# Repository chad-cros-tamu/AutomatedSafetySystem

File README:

The hardware folder folder is for the hardware designs of the main controller board, the light curtain and the proximity sensor
The firmware folder is for the code that runs the MCU.

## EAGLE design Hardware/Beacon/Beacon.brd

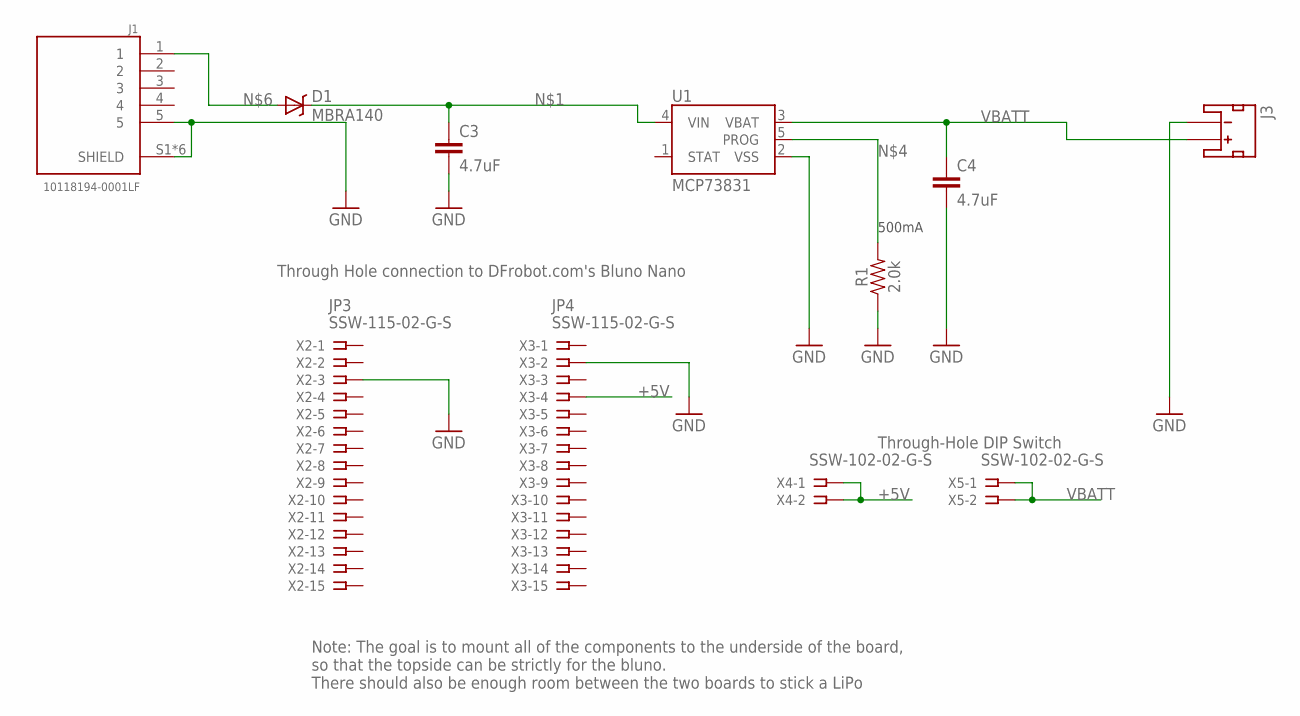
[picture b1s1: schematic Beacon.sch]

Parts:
C3, C4: 4.7uF; 0603
D1: MBRA140; SMA-DIODE
J1: 10118194-0001LF; AMPHENOL_10118194-0001LF
J3: JST_2MM_MALE; JST-2-SMD
R1: 2.0k; 0603
U1: MCP73831; SOT23-5
X2, X3: SSW-115-02-G-S
X4, X5: SSW-102-02-G-S

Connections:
+5V: X3.4, X4.1, X4.2
GND: C3.2, C4.2, J1.5, J1.S1 (SHIELD), J1.S2 (SHIELD), J1.S3 (SHIELD), J1.S4 (SHIELD), J1.S5 (SHIELD), J1.S6 (SHIELD), J3.1 (-), R1.1, U1.2 (VSS), X2.3, X3.2
unnamed: C3.1, D1.C, U1.4 (VIN)
unnamed: R1.2, U1.5 (PROG)
unnamed: D1.A, J1.1
VBATT: C4.1, J3.2 (+), U1.3 (VBAT), X5.1, X5.2

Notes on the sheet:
500mA
JP3
JP4
Through-Hole DIP Switch
Through Hole connection to DFrobot.com's Bluno Nano
Note: The goal is to mount all of the components to the underside of the board, so that the topside can be strictly for the bluno. There should also be enough room between the two boards to stick a LiPo

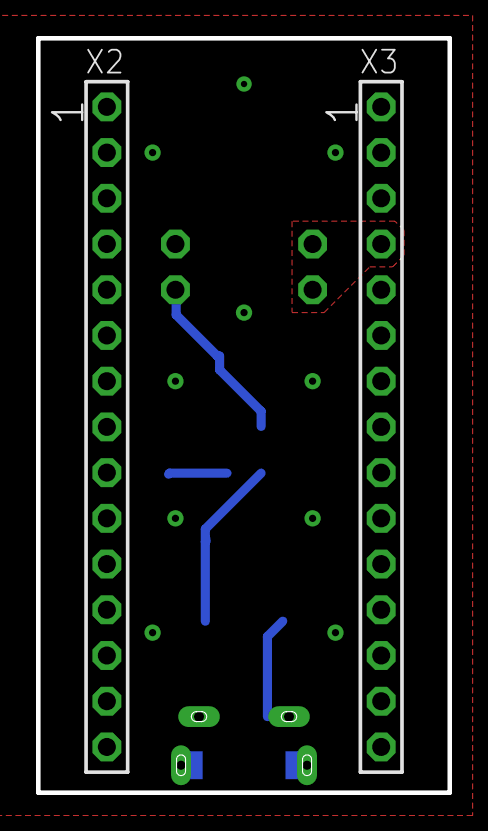
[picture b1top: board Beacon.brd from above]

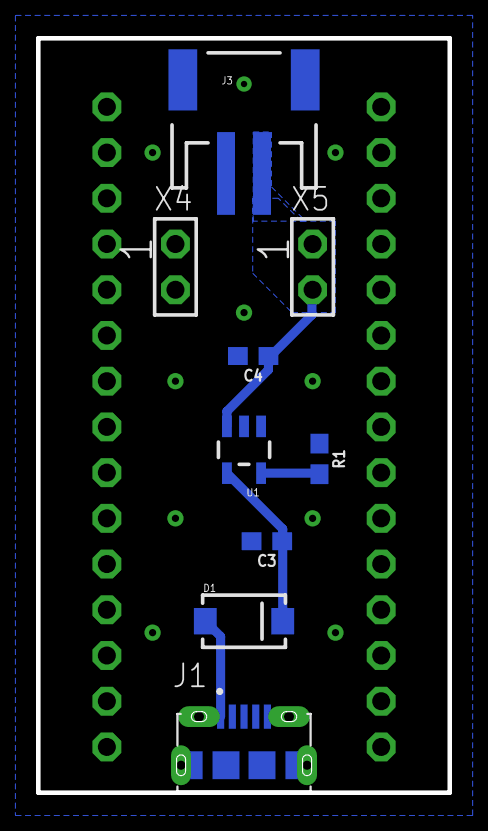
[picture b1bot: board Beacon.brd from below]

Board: 2 copper layers, 22.9 x 41.9 mm, 11 parts (9 on the bottom side), 6 nets.

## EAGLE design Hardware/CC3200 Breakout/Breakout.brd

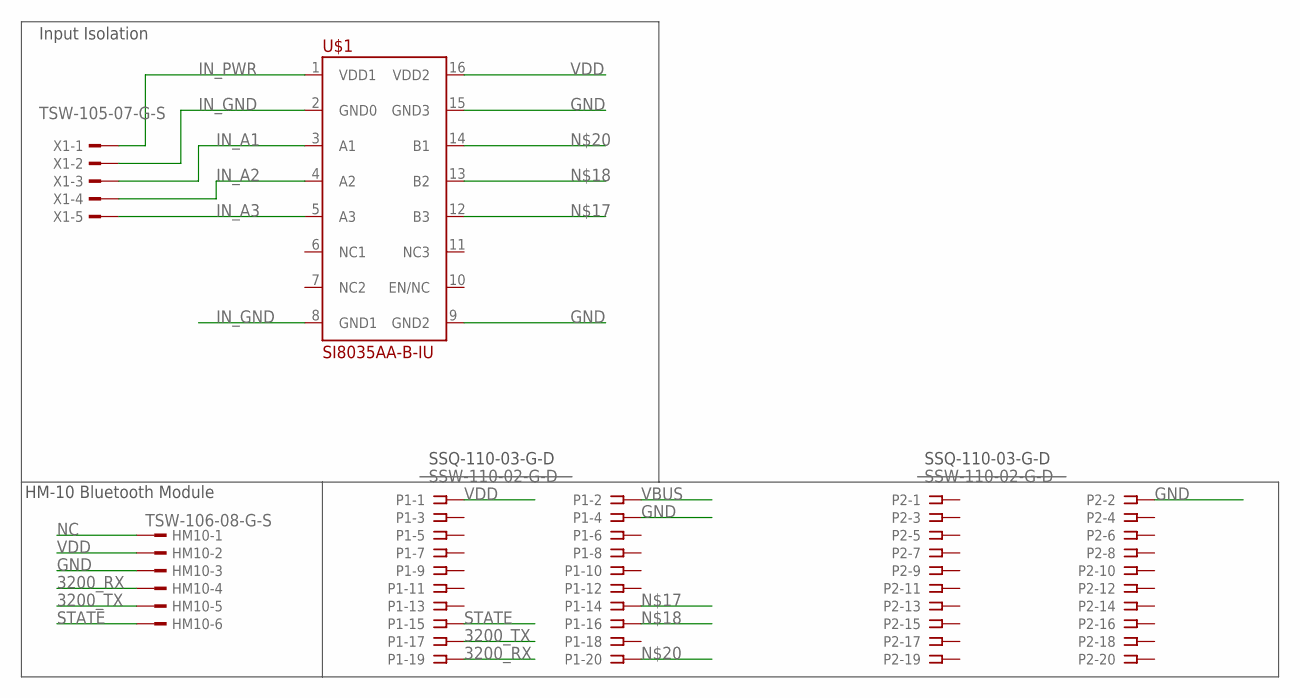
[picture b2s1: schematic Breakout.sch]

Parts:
HM10: TSW-106-08-G-S; TSW-106-XX-G-S
P1, P2: SSW-110-02-G-D
U$1: SI8035AA-B-IU; SOP63P602X175-16N
X1: TSW-105-07-G-S; TSW-105-XX-G-S

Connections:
3200_RX: HM10.4, P1.19
3200_TX: HM10.5, P1.17
GND: HM10.3, P1.4, P2.2, U$1.9 (GND2), U$1.15 (GND3)
IN_A1: U$1.3 (A1), X1.3
IN_A2: U$1.4 (A2), X1.4
IN_A3: U$1.5 (A3), X1.5
IN_GND: U$1.2 (GND0), U$1.8 (GND1), X1.2
IN_PWR: U$1.1 (VDD1), X1.1
unnamed: P1.14, U$1.12 (B3)
unnamed: P1.16, U$1.13 (B2)
unnamed: P1.20, U$1.14 (B1)
NC: HM10.1
STATE: HM10.6, P1.15
VBUS: P1.2
VDD: HM10.2, P1.1, U$1.16 (VDD2)

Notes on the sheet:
HM-10 Bluetooth Module
SSQ-110-03-G-D
Input Isolation

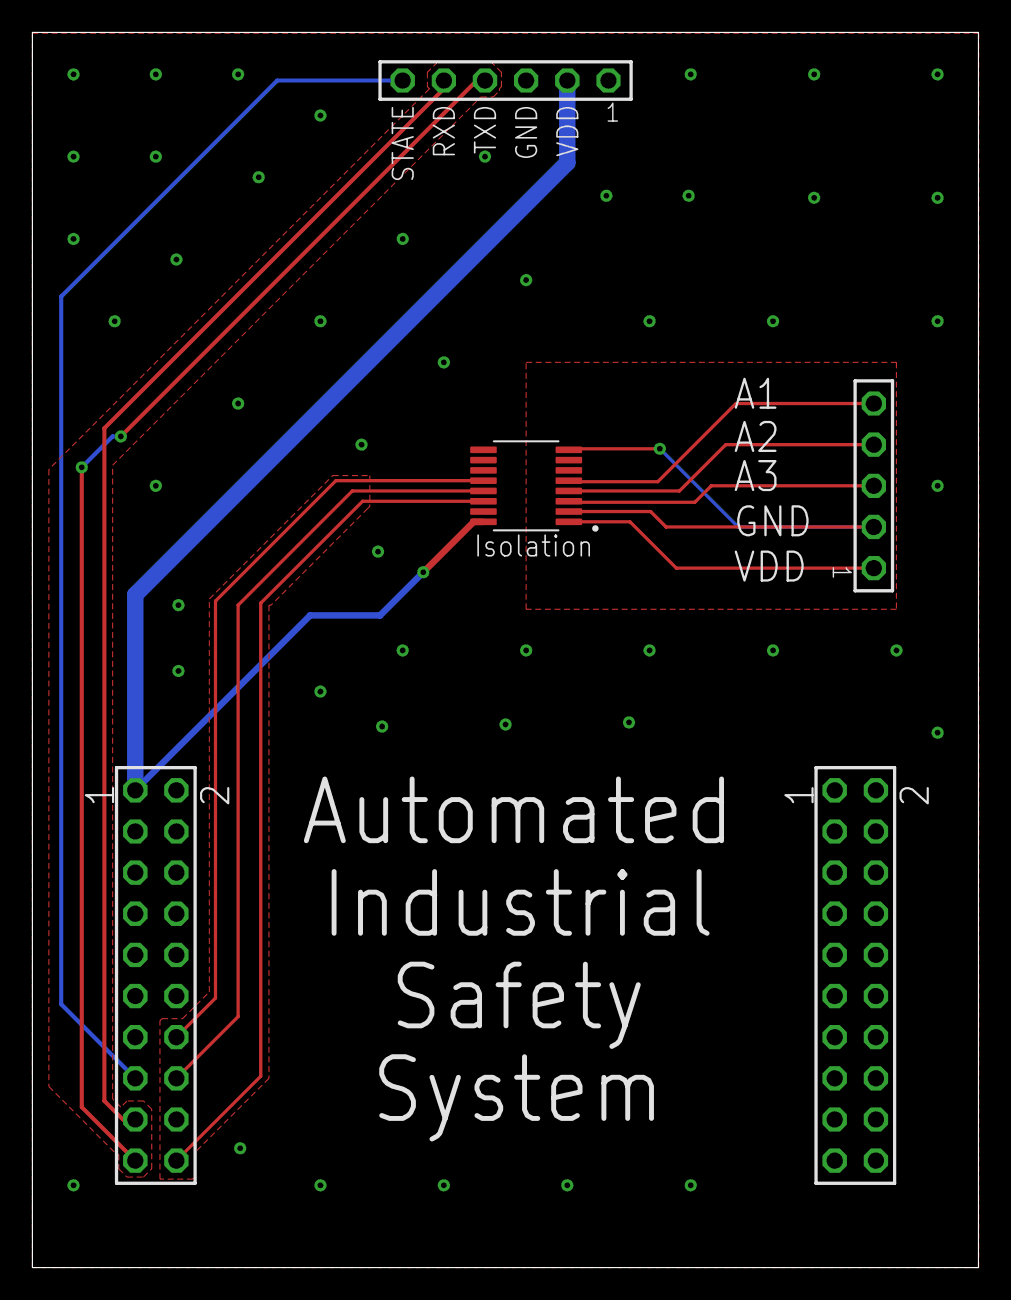
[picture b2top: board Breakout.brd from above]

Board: 2 copper layers, 58.4 x 76.3 mm, 5 parts (0 on the bottom side), 13 nets.

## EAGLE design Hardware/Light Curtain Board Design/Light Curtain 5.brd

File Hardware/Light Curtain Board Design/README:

Design and validation of light curtain sensor

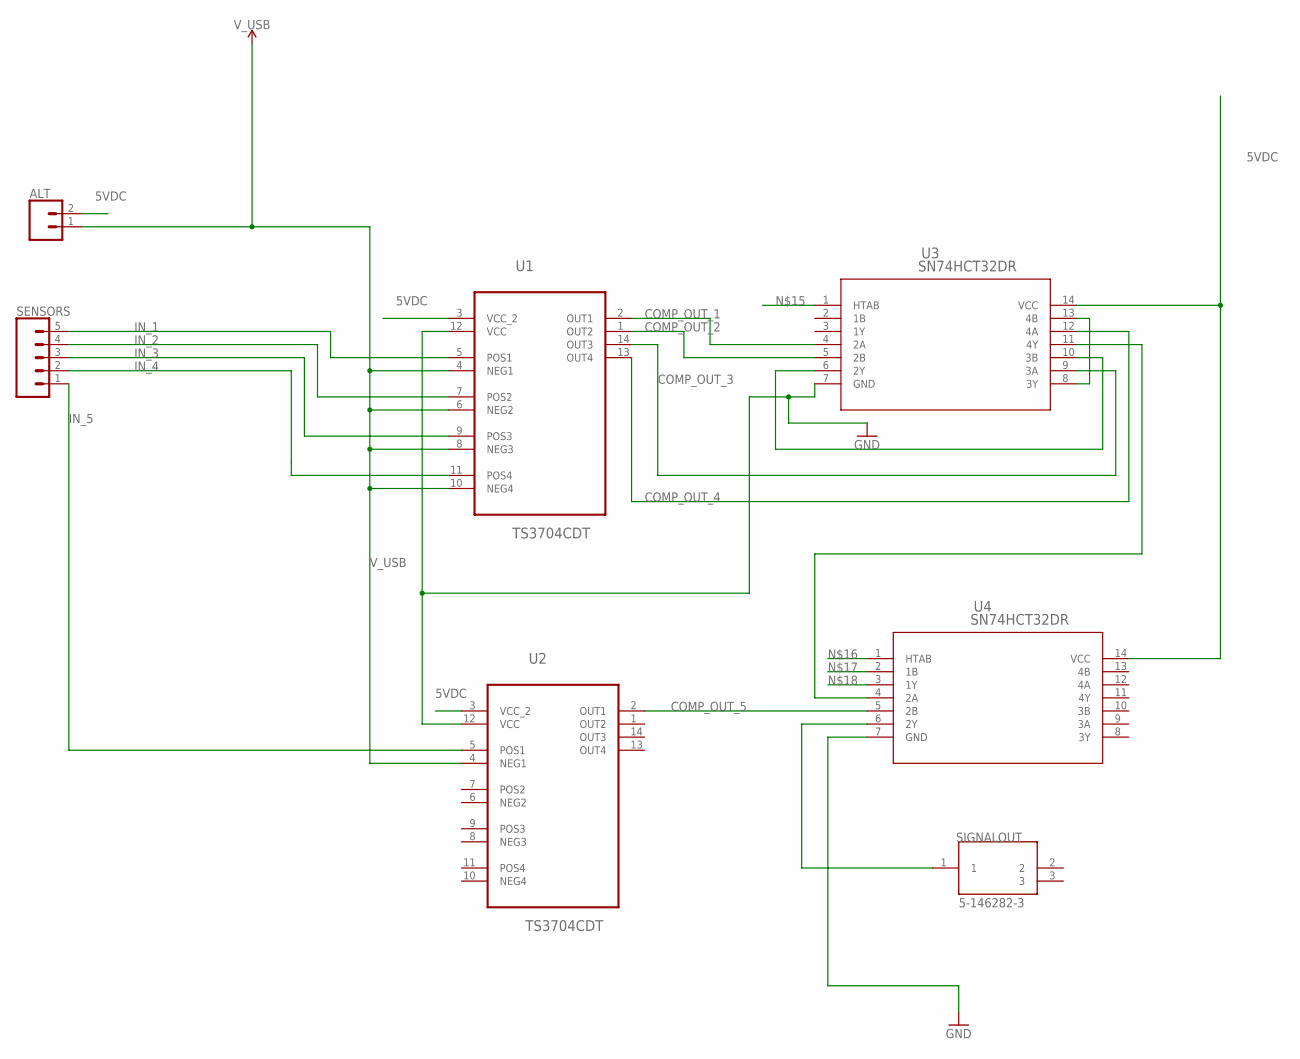
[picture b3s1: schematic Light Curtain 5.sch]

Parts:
ALT: CONN_02; 1X02
SENSORS: CONN_05; 1X05
SIGNALOUT: 5-146282-3; TE_5-146282-3
U1, U2: TS3704CDT; SOIC127P600X175-14N
U3, U4: SN74HCT32DR; D14

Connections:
5VDC: ALT.2, U1.3 (VCC_2), U2.3 (VCC_2), U3.14 (VCC), U4.14 (VCC)
COMP_OUT_1: U1.2 (OUT1), U3.4 (2A)
COMP_OUT_2: U1.1 (OUT2), U3.5 (2B)
COMP_OUT_3: U1.14 (OUT3), U3.9 (3A)
COMP_OUT_4: U1.13 (OUT4), U3.12 (4A)
COMP_OUT_5: U2.2 (OUT1), U4.5 (2B)
GND: U1.12 (VCC), U2.12 (VCC), U3.7 (GND), U4.7 (GND)
IN_1: SENSORS.5, U1.5 (POS1)
IN_2: SENSORS.4, U1.7 (POS2)
IN_3: SENSORS.3, U1.9 (POS3)
IN_4: SENSORS.2, U1.11 (POS4)
IN_5: SENSORS.1, U2.5 (POS1)
unnamed: U3.6 (2Y), U3.10 (3B)
unnamed: U3.8 (3Y), U3.13 (4B)
unnamed: U3.11 (4Y), U4.4 (2A)
unnamed: SIGNALOUT.1, U4.6 (2Y)
V_USB: ALT.1, U1.4 (NEG1), U1.6 (NEG2), U1.8 (NEG3), U1.10 (NEG4), U2.4 (NEG1)

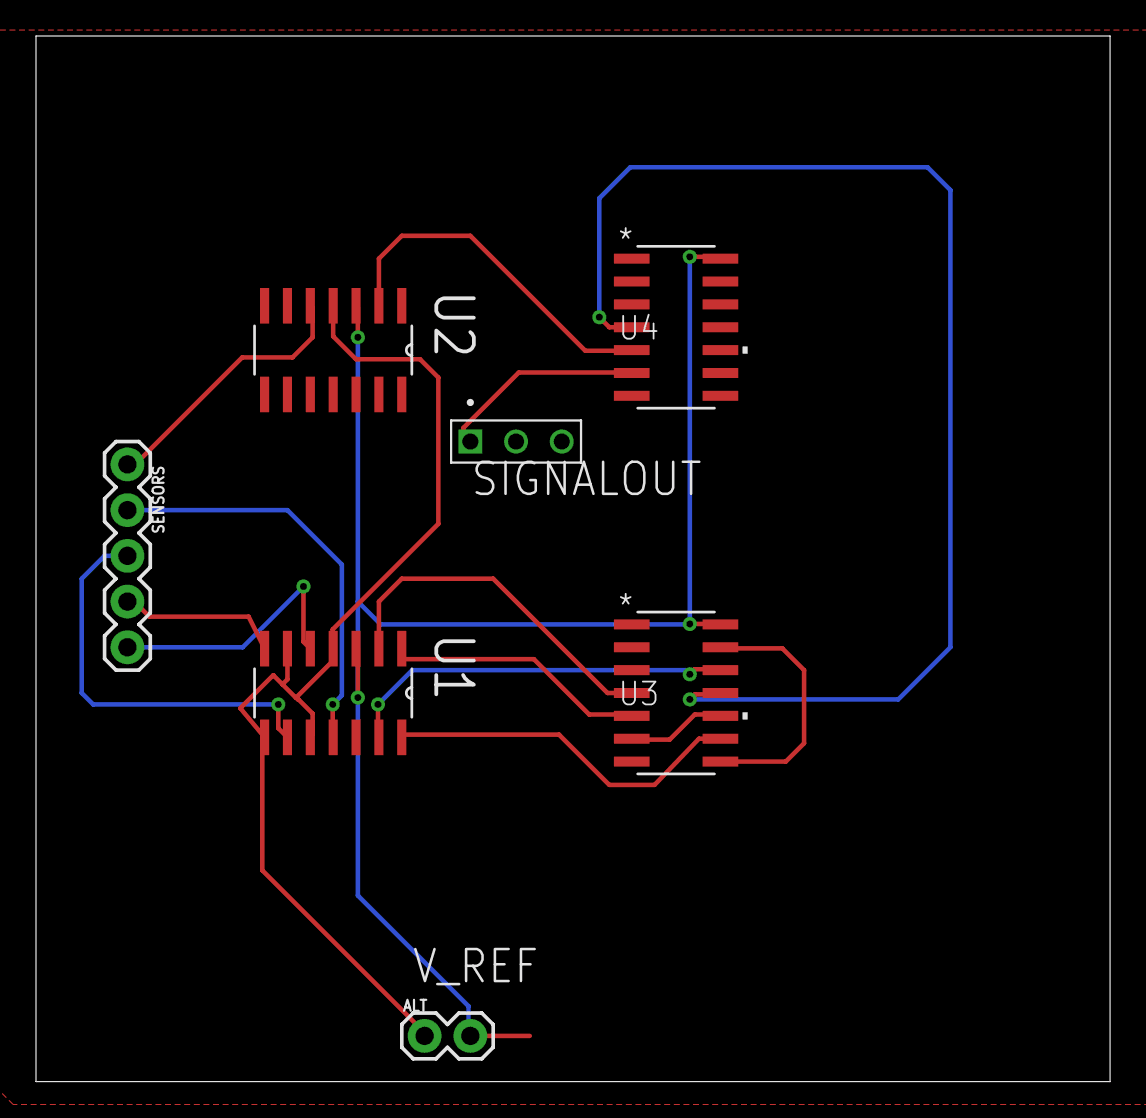
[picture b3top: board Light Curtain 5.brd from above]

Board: 2 copper layers, 59.7 x 58.1 mm, 7 parts (0 on the bottom side), 17 nets.

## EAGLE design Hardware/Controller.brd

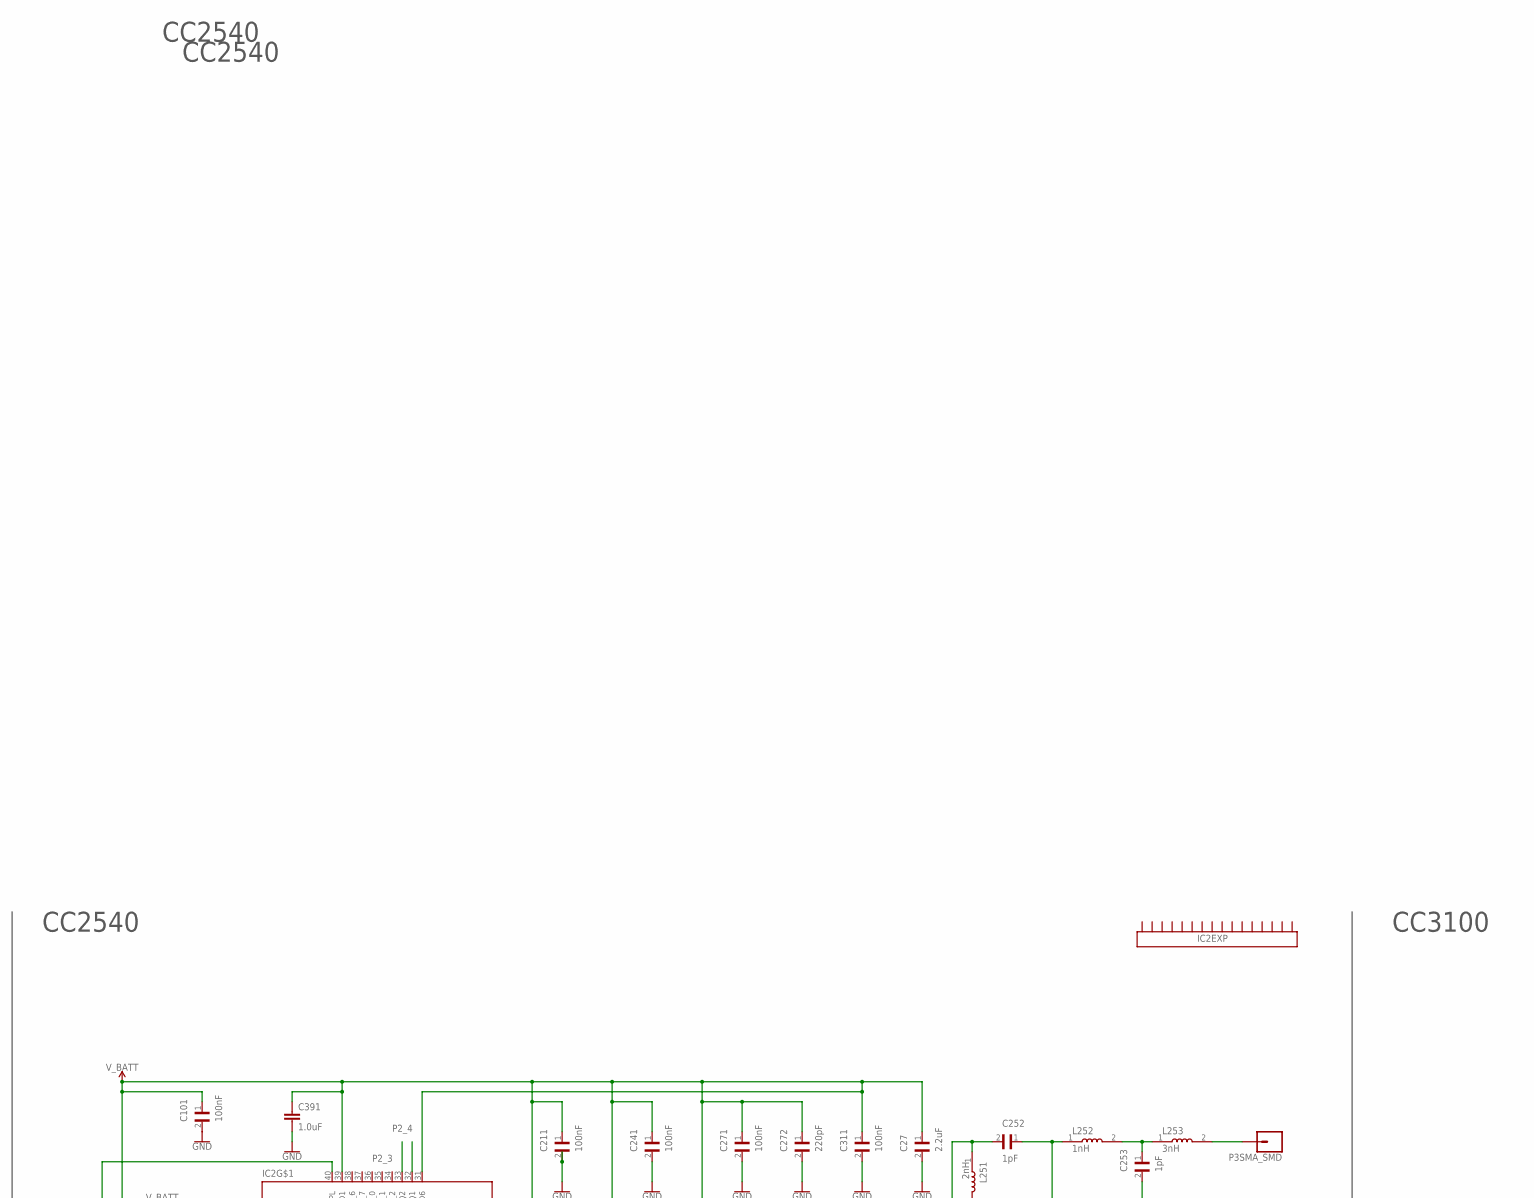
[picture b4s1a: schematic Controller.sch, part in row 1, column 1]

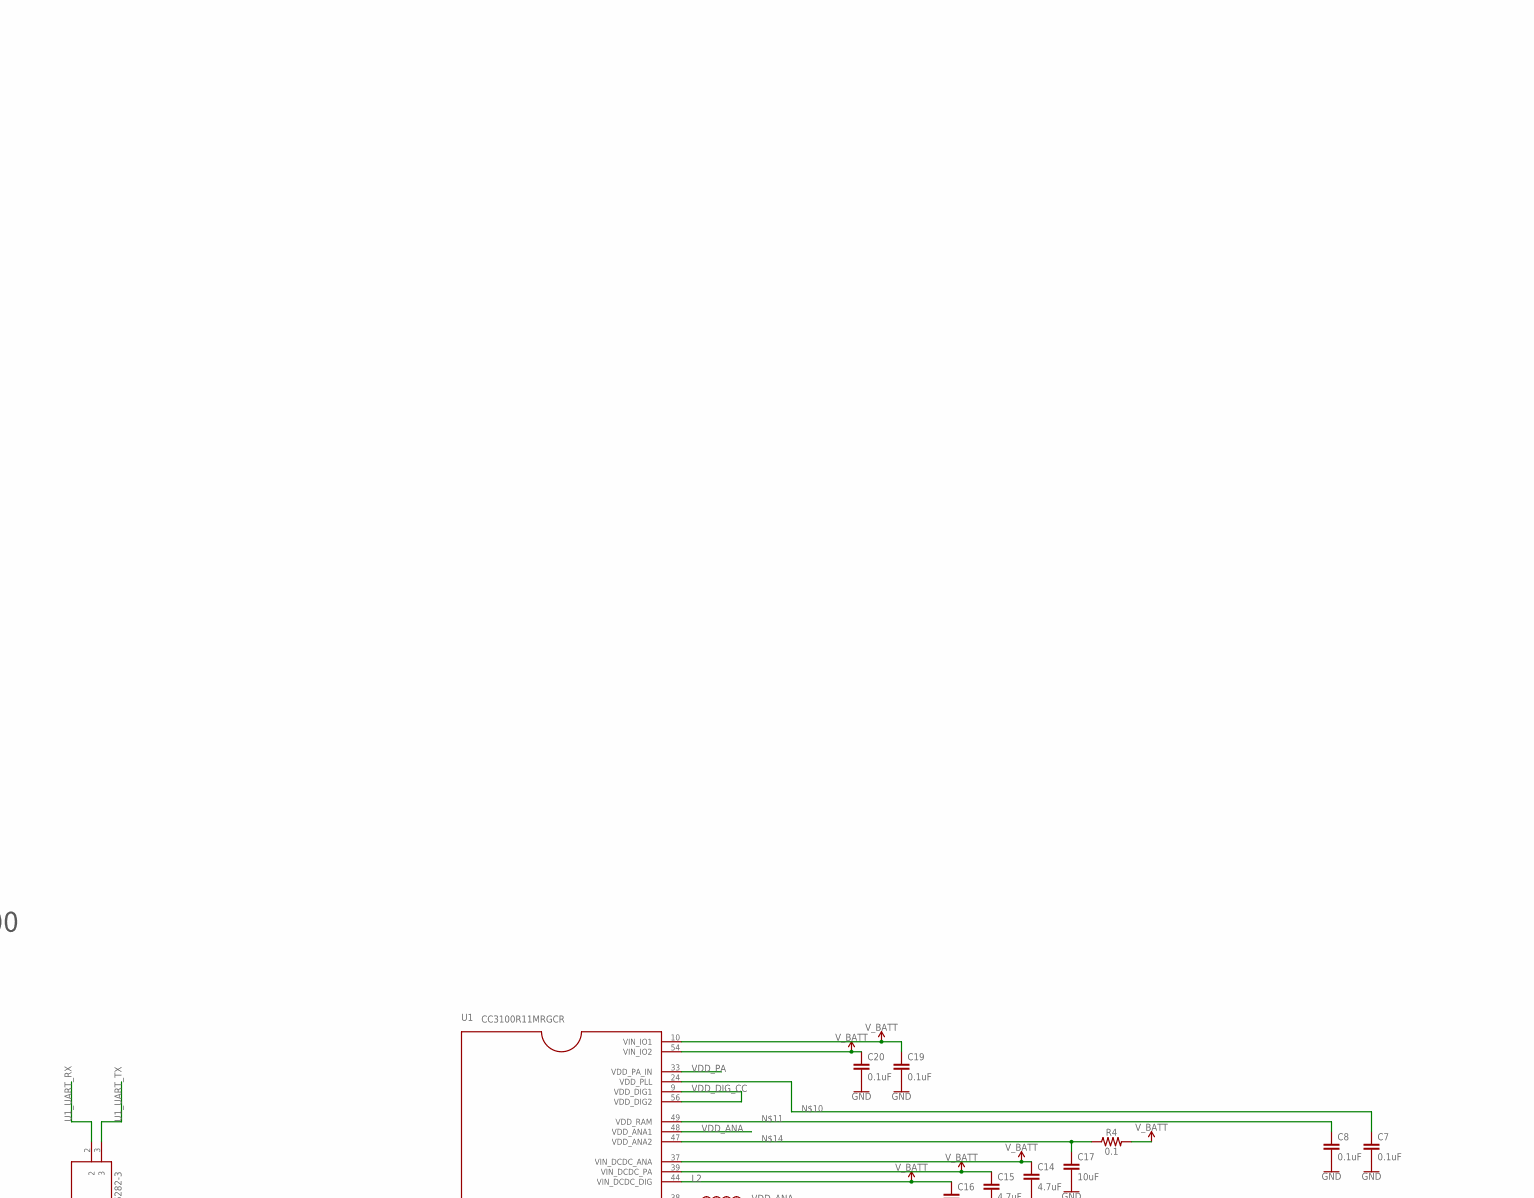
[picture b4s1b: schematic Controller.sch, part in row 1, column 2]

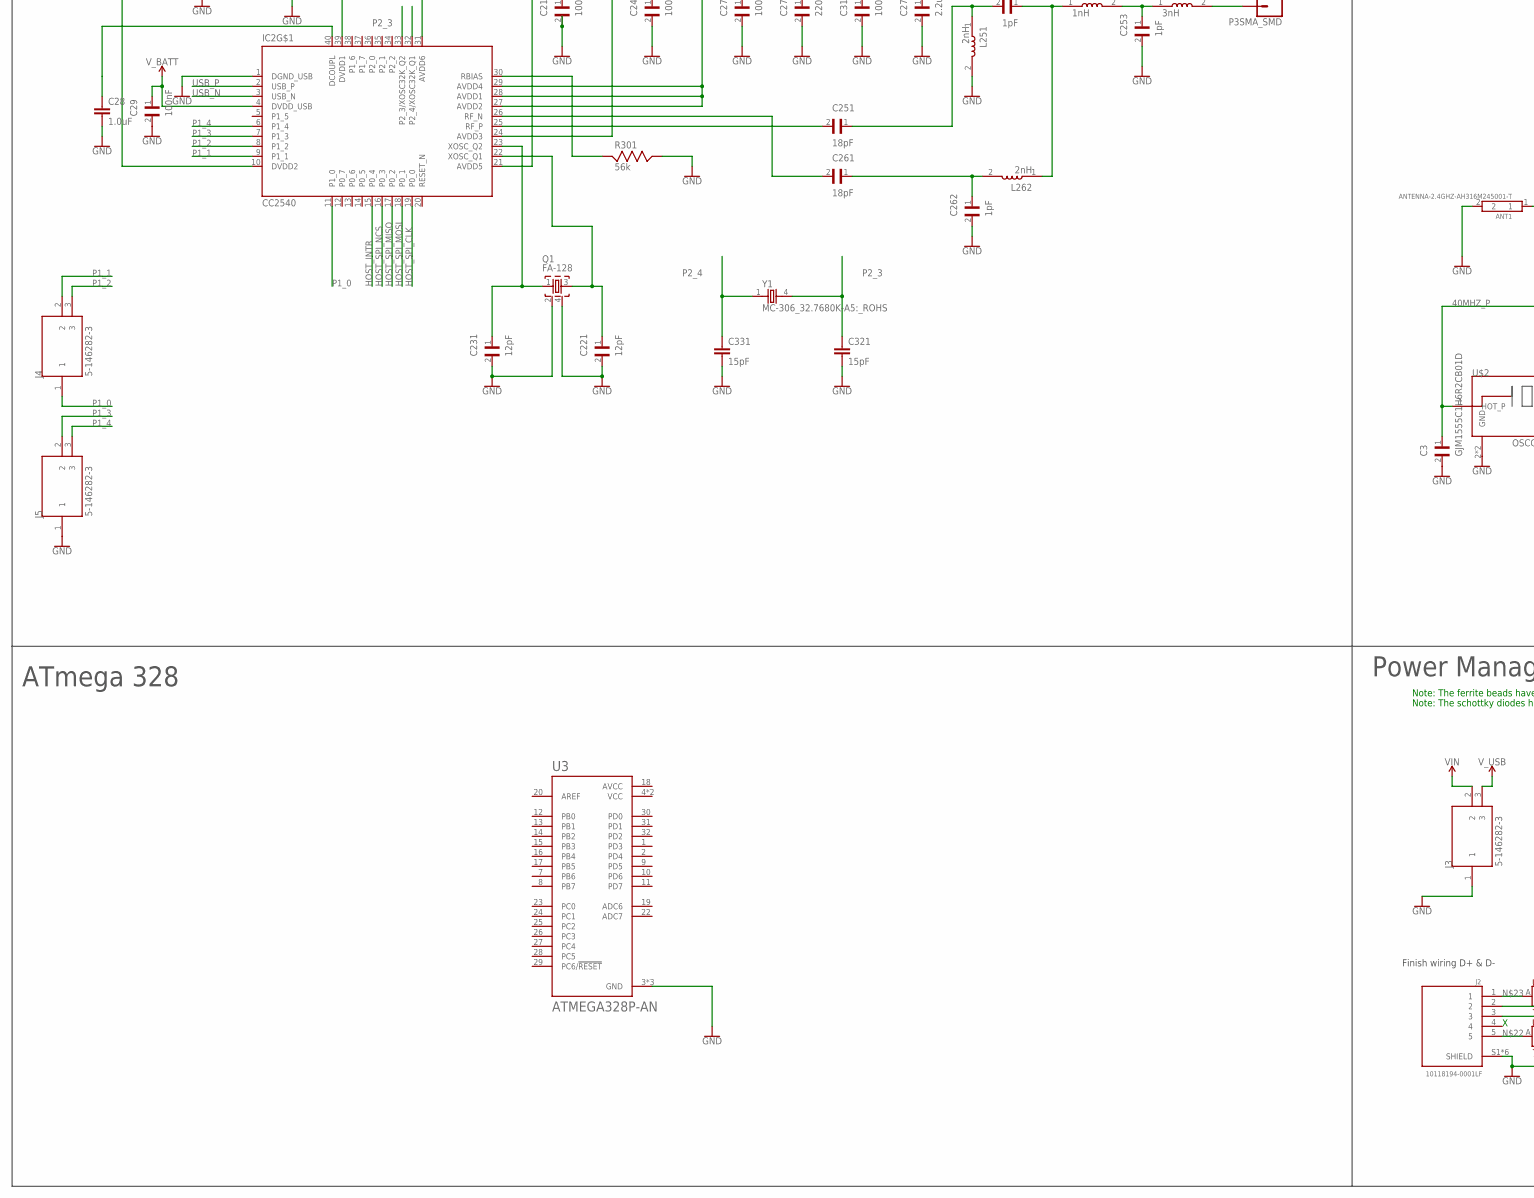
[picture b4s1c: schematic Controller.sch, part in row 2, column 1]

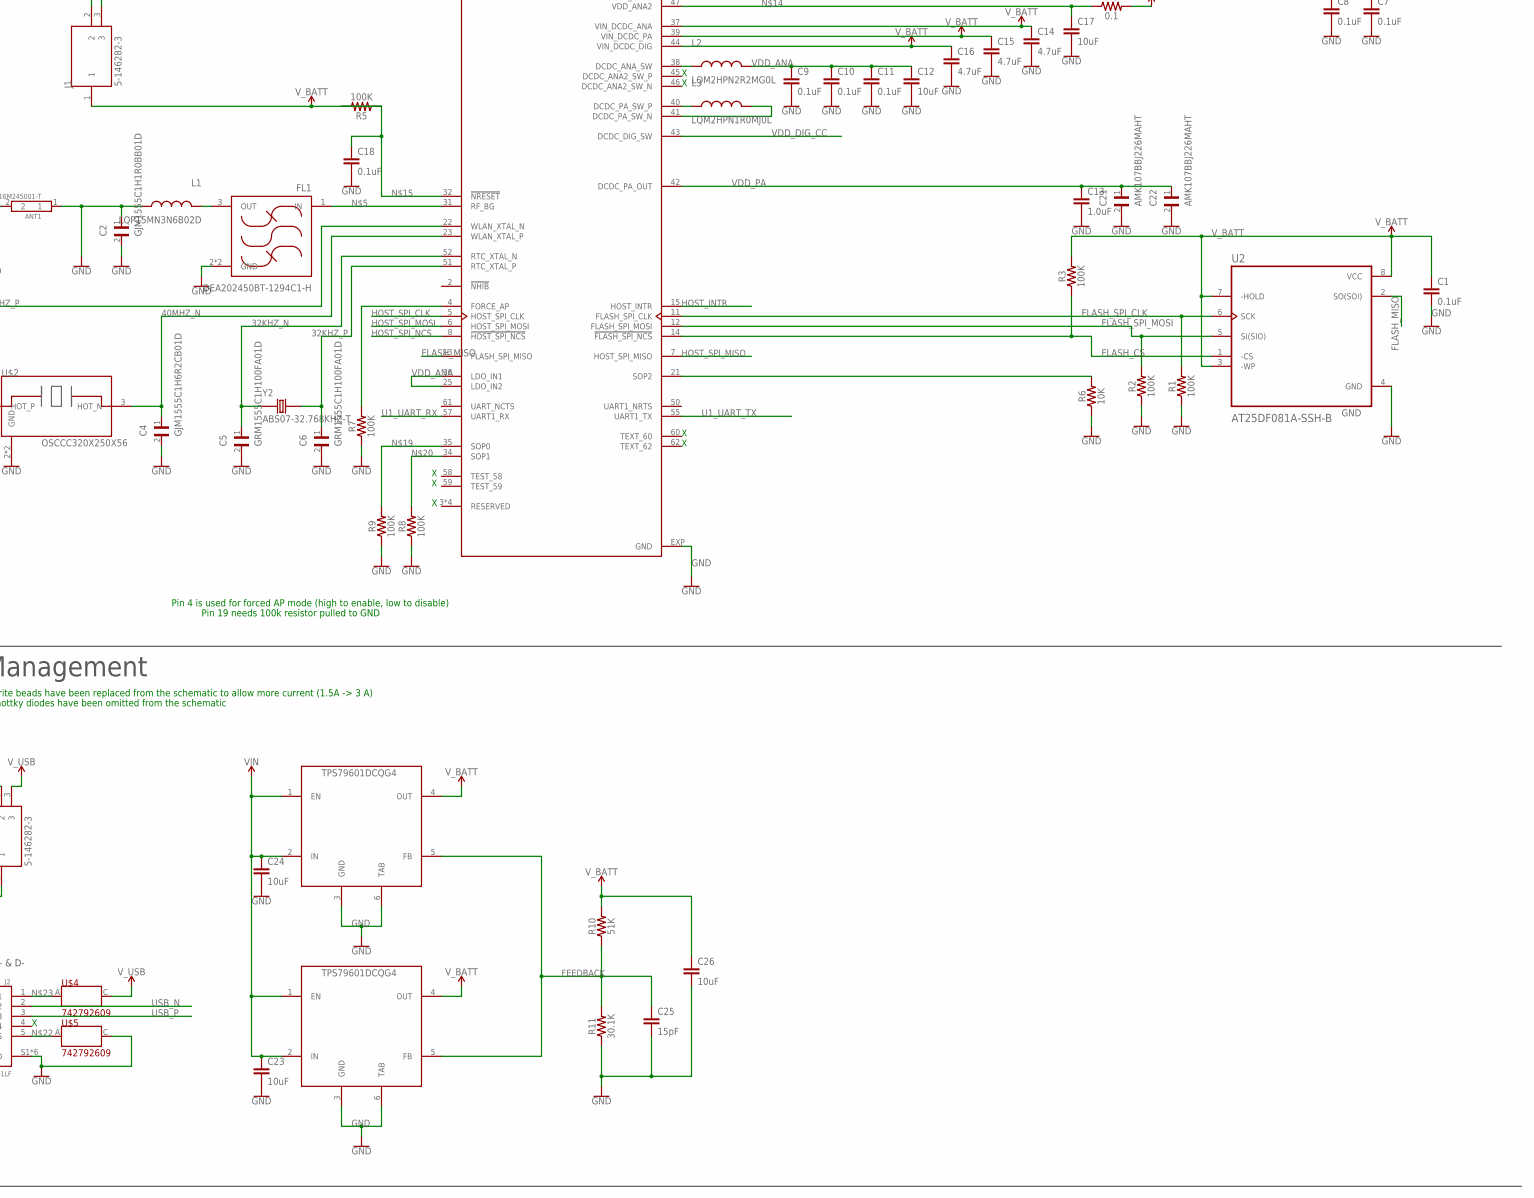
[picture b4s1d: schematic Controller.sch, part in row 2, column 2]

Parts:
ANT1: ANTENNA-2.4GHZ-AH316M245001-T; ANT2-SMD-3.2X1.6X0.5MM
C1, C7, C8, C9, C10, C11, C18, C19, C20: 0.1uF; 0402
C2: GJM1555C1H1R0BB01D; CAPC1005X55N
C3, C4: GJM1555C1H6R2CB01D; CAPC1005X55N
C5, C6: GRM1555C1H100FA01D; CAPC1005X55N
C12, C17, C23, C24, C26: 10uF; 0603
C13, C28, C391: 1.0uF; 0402
C14, C15, C16: 4.7uF; 0402-TIGHT
C21, C22: AMK107BBJ226MAHT; CAPC1608X95N
C25, C321, C331: 15pF; 0402
C27: 2.2uF; CAPC1005X55N
C29, C101, C211, C241, C271, C311: 100nF; CAPC1005X55N
C221, C231: 12pF; CAPC1005X55N
C251, C261: 18pF; CAPC1005X55N
C252, C253, C262: 1pF; CAPC1005X55N
C272: 220pF; CAPC1005X55N
FL1: DEA202450BT-1294C1-H; FIL_DEA202450BT-1294C1-H
IC2: CC2540; QFN40-6X6
J1, J3, J4, J5: 5-146282-3; TE_5-146282-3
J2: 10118194-0001LF; AMPHENOL_10118194-0001LF
L1: LQP15MN3N6B02D; INDC0402X01
L2: LQM2HPN2R2MG0L; INDC1008X04
L3: LQM2HPN1R0MJ0L; INDC1008X04
L251, L262: 2nH; INDC1005X45
L252: 1nH; INDC1005X45
L253: 3nH; INDC1005X45
P3SMA_SMD: CONN_01; 1X01
Q1: FA-128
R1, R2, R3, R5, R7, R8, R9: 100K; 0402
R4: 0.1; 0603
R6: 10K; 0402
R10: 51K; 0402
R11: 30.1K; 0402
R301: 56k; RESC1005X40
U1: CC3100R11MRGCR; QFN50P900X900X100-65N
U2: AT25DF081A-SSH-B; SOIC127P600X175-8N
U3: ATMEGA328P-AN; QFP80P900X900X120-32N
U$1, U$3: TPS79601DCQG4; SOT127P706X180-6N
U$2: OSCCC320X250X56
U$4, U$5: 742792609; LEDM1608X80
Y1: MC-306_32.7680K-A5:_ROHS; OSCL550P800X320X254-4N
Y2: ABS07-32.768KHZ-T; XTAL_ABS07-32.768KHZ-T

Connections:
32KHZ_N: C5.1, U1.52 (RTC_XTAL_N), Y2.1
32KHZ_P: C6.1, U1.51 (RTC_XTAL_P), Y2.2
40MHZ_N: C4.1, U1.23 (WLAN_XTAL_P), U$2.3 (HOT_N)
40MHZ_P: C3.1, U1.22 (WLAN_XTAL_N), U$2.1 (HOT_P)
AVCC: U3.18 (AVCC)
DCDC_ANA2_SW_N: U1.46 (DCDC_ANA2_SW_N)
DCDC_ANA2_SW_P: U1.45 (DCDC_ANA2_SW_P)
FEEDBACK: C25.1, R10.1, R11.2, U$1.5 (FB), U$3.5 (FB)
FLASH_CS: R3.1, U1.14 (!FLASH_SPI_NCS), U2.1 (-CS)
FLASH_MISO: U1.13 (FLASH_SPI_MISO), U2.2 (SO(SOI))
FLASH_SPI_CLK: R1.2, U1.11 (FLASH_SPI_CLK), U2.6 (SCK)
FLASH_SPI_MOSI: R2.2, U1.12 (FLASH_SPI_MOSI), U2.5 (SI(SIO))
GND: ANT1.1, ANT1.2, C1.2, C2.1, C2.2, C3.2, C4.2, C5.2, C6.2, C7.2, C8.2, C9.2, C10.2, C11.2, C12.2, C13.2, C14.2, C15.2, C16.2, C17.2, C18.2, C19.2, C20.2, C21.2, C22.2, C23.2, C24.2, C25.2, C26.2, C27.2, C28.2, C29.2, C101.2, C211.2, C221.2, C231.2, C241.2, C253.2, C262.2, C271.2, C272.2, C311.2, C321.2, C331.2, C391.2, FL1.2 (GND), FL1.4 (GND), J2.S1 (SHIELD), J2.S2 (SHIELD), J2.S3 (SHIELD), J2.S4 (SHIELD), J2.S5 (SHIELD), J2.S6 (SHIELD), J3.1, J5.1, L1.2, L251.2, Q1.2, Q1.4, R1.1, R2.1, R6.1, R7.1, R8.1, R9.1, R11.1, R301.2, U1.EXP (GND), U2.4 (GND), U3.3 (GND), U3.5 (GND), U3.21 (GND), U$1.3 (GND), U$1.6 (TAB), U$2.2 (GND), U$2.4 (GND), U$3.3 (GND), U$3.6 (TAB), U$5.C
HOST_INTR: IC2.15 (P0_4), U1.15 (HOST_INTR)
HOST_SPI_CLK: IC2.19 (P0_0), U1.5 (HOST_SPI_CLK)
HOST_SPI_MISO: IC2.17 (P0_2), U1.7 (HOST_SPI_MISO)
HOST_SPI_MOSI: IC2.18 (P0_1), U1.6 (HOST_SPI_MOSI)
HOST_SPI_NCS: IC2.16 (P0_3), U1.8 (!HOST_SPI_NCS)
unnamed: FL1.1 (IN), U1.31 (RF_BG)
unnamed: FL1.3 (OUT), L1.1
unnamed: C7.1, U1.24 (VDD_PLL)
unnamed: C8.1, U1.49 (VDD_RAM)
unnamed: R6.2, U1.21 (SOP2)
unnamed: L2.1, U1.38 (DCDC_ANA_SW)
unnamed: C17.1, R4.1, U1.47 (VDD_ANA2)
unnamed: C18.1, R5.1, U1.32 (!NRESET)
unnamed: L3.1, U1.40 (DCDC_PA_SW_P)
unnamed: L3.2, U1.41 (DCDC_PA_SW_N)
unnamed: R7.2, U1.4 (FORCE_AP)
unnamed: R9.2, U1.35 (SOP0)
unnamed: R8.2, U1.34 (SOP1)
unnamed: J2.5, U$5.A
unnamed: J2.1, U$4.A
unnamed: C251.2, IC2.25 (RF_P)
unnamed: C261.2, IC2.26 (RF_N)
unnamed: C251.1, C252.2, L251.1
unnamed: C261.1, C262.1, L262.2
unnamed: C252.1, L252.1, L262.1
unnamed: C253.1, L252.2, L253.1
unnamed: L253.2, P3SMA_SMD.1
unnamed: C231.1, IC2.23 (XOSC_Q2), Q1.1
unnamed: C221.1, IC2.22 (XOSC_Q1), Q1.3
unnamed: C28.1, IC2.40 (DCOUPL)
unnamed: IC2.30 (RBIAS), R301.1
P1_0: IC2.11 (P1_0), J4.1
P1_1: IC2.9 (P1_1), J4.2
P1_2: IC2.8 (P1_2), J4.3
P1_3: IC2.7 (P1_3), J5.2
P1_4: IC2.6 (P1_4), J5.3
P2_3: C321.1, IC2.33 (P2_3/XOSC32K_Q2), Y1.4
P2_4: C331.1, IC2.32 (P2_4/XOSC32K_Q1), Y1.1
U1_UART_RX: J1.2, U1.57 (UART1_RX)
U1_UART_TX: J1.3, U1.55 (UART1_TX)
USB_N: IC2.3 (USB_N), J2.2
USB_P: IC2.2 (USB_P), J2.3
VCC: U3.4 (VCC), U3.6 (VCC)
VDD_ANA: C9.1, C10.1, C11.1, C12.1, L2.2, U1.25 (LDO_IN2), U1.36 (LDO_IN1), U1.48 (VDD_ANA1)
VDD_DIG_CC: U1.9 (VDD_DIG1), U1.43 (DCDC_DIG_SW), U1.56 (VDD_DIG2)
VDD_PA: C13.1, C21.1, C22.1, U1.33 (VDD_PA_IN), U1.42 (DCDC_PA_OUT)
VIN: C23.1, C24.1, J3.2, U$1.1 (EN), U$1.2 (IN), U$3.1 (EN), U$3.2 (IN)
V_BATT: C1.1, C14.1, C15.1, C16.1, C19.1, C20.1, C26.1, C27.1, C29.1, C101.1, C211.1, C241.1, C271.1, C272.1, C311.1, C391.1, IC2.4 (DVDD_USB), IC2.10 (DVDD2), IC2.21 (AVDD5), IC2.24 (AVDD3), IC2.27 (AVDD2), IC2.28 (AVDD1), IC2.29 (AVDD4), IC2.31 (AVDD6), IC2.39 (DVDD1), J1.1, R3.2, R4.2, R5.2, R10.2, U1.10 (VIN_IO1), U1.37 (VIN_DCDC_ANA), U1.39 (VIN_DCDC_PA), U1.44 (VIN_DCDC_DIG), U1.54 (VIN_IO2), U2.3 (-WP), U2.7 (-HOLD), U2.8 (VCC), U$1.4 (OUT), U$3.4 (OUT)
V_USB: J3.3, U$4.C

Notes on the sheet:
Pin 4 is used for forced AP mode (high to enable, low to disable)
Pin 19 needs 100k resistor pulled to GND
CC3100
Power Management
Note: The ferrite beads have been replaced from the schematic to allow more current (1.5A -> 3 A)
Note: The schottky diodes have been omitted from the schematic
Finish wiring D+ & D-
CC2540
ATmega 328

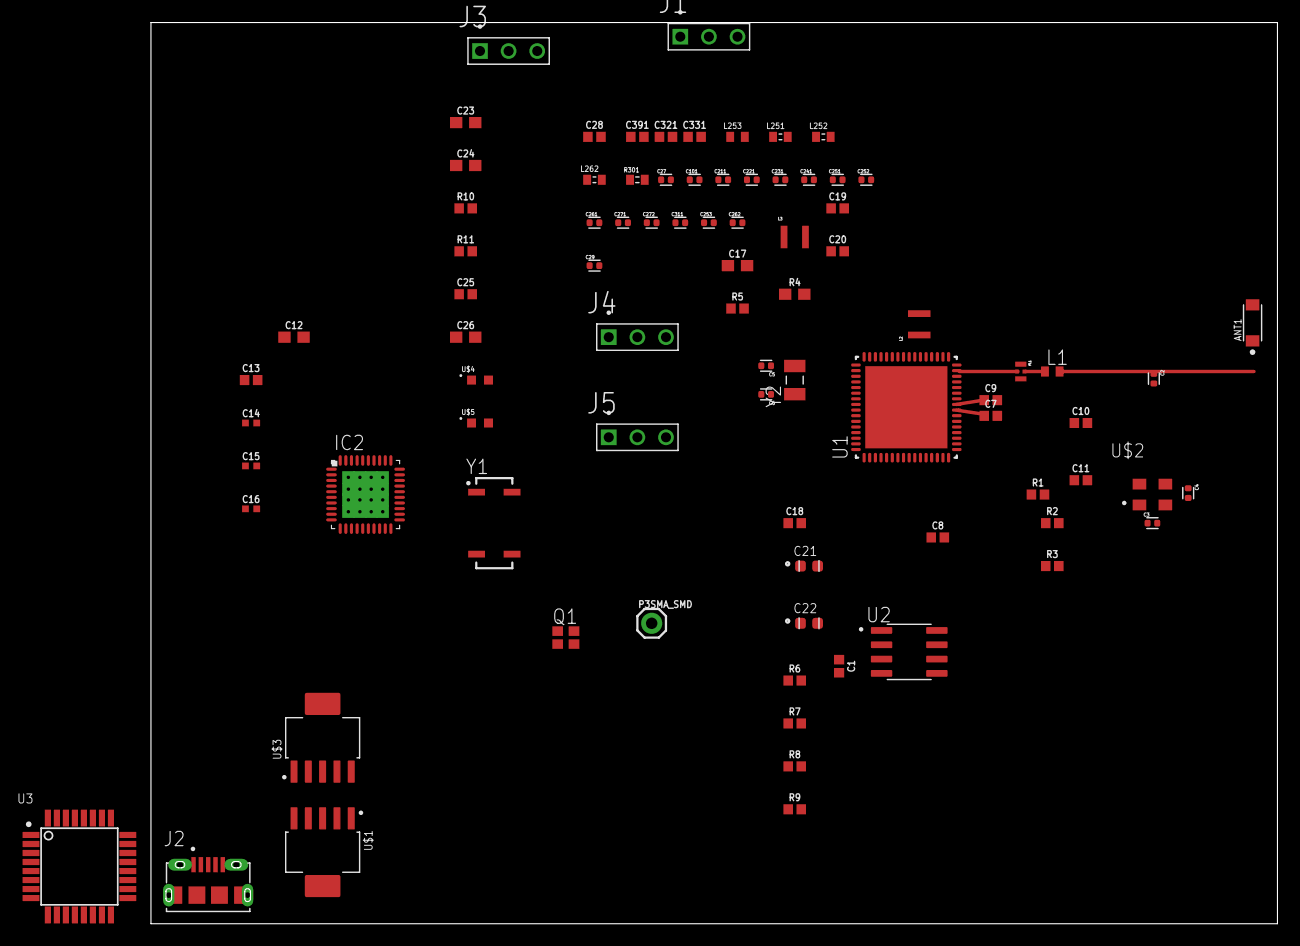
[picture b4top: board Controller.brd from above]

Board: 2 copper layers, 100.0 x 80.0 mm, 84 parts (0 on the bottom side), 59 nets.

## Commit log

2019-09-05 Create ChadWeeklyUpdates
    Created new text file for Chad's Weekly updates to present to TA
2019-09-05 Added Schematic and Layout files to repository
2019-09-05 Updated git to contain current working files
2019-09-05 Created .gitignore
    File will be used to ignore file type uploads
2019-09-05 Update .gitignore
    Fixed ignoring for DS_Store files
2019-09-05 Removed DS_Store file
2019-09-05 Webpage
2019-09-05 Jaime's Weekly Updates
2019-09-05 Create Andres Weekly Update
2019-09-05 Update Jaime_Weekly_Updates
2019-09-05 Update ChadWeeklyUpdates
2019-09-12 Updated ChadWeeklyUpdates
    Week of Sept 9
2019-09-13 Update Andres Weekly Update
2019-10-03 Removed outdated hardware
2019-10-03 Updated Hardware
    Added PCB layouts + schematics to their appropriate folders
2019-10-03 Updated to ignore files
2019-10-03 Removed unneeded files
2019-10-03 Create README
    Added a description of the problems found with the PCB
2019-11-26 Updated the breakout schematics
2019-11-26 Removed unneeded BLE Firmware
2019-11-26 Removed unneeded versions of WIFI Code
2019-11-26 Added WIFI Controller Firmware
    File is responsible for interfacing the Bluetooth module, the Hardware sensors, and the Webpage
2019-11-26 Added schematic + layout for the bluetooth beacons
2019-11-26 Removed License
2019-12-04 Webpage
    Final code for the webpage
2019-12-04 resubmit
    resubmitted
2019-12-04 Final ECEN 404 code for the Webpage
2019-12-04 resubmit
2019-12-04 Final code for the webpage

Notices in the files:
parts and their libraries:
SparkFun-DiscreteSemi: Licensing: CC v3.0 Share-Alike You are welcome to use this library for commercial purposes.
SparkFun-Capacitors: Licensing: Creative Commons ShareAlike 4.0 International - https://creativecommons.org/licenses/by-sa/4.0
